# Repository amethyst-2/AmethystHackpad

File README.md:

<h1> Amethyst Hackpad  </h1>
Welcome to my project.  
Its a cutie made my be :)  
with amethyst colors as my name  

<h2> Design  </h2>
Below are all the images of hackpad  

Case :-  

Bottom layer :-  
  
For the pcb to rest on i have added a small ridge ( with chamfer on the below )  

Top layer :-  

<h2> Electronics </h2>  

Now let's get to the electronics part!  
Schematics ( Made in KiCad ) :-  

PCB :-  

<h2> Bill of Materials  </h2>
And finally here is the all the materials I used :-  

|      |Component Used            |      |Quantity|
|------|--------------------------|------|--------|
|      |                          |      |        |
|1     |Seeed XIAO RP2040         |      |1       |
|      |                          |      |        |
|2     |MX-Style switches         |      |16      |
|      |                          |      |        |
|3     |Through-hole 1N4148 Diodes|      |16      |
|      |                          |      |        |
|4     |0.91 inch OLED            |      |1       |
|      |                          |      |        |
|5     |Blank DSA keycaps         |      |16      |
|      |                          |      |        |
|6     |SK6812 MINI-E LEDs        |      |16      |

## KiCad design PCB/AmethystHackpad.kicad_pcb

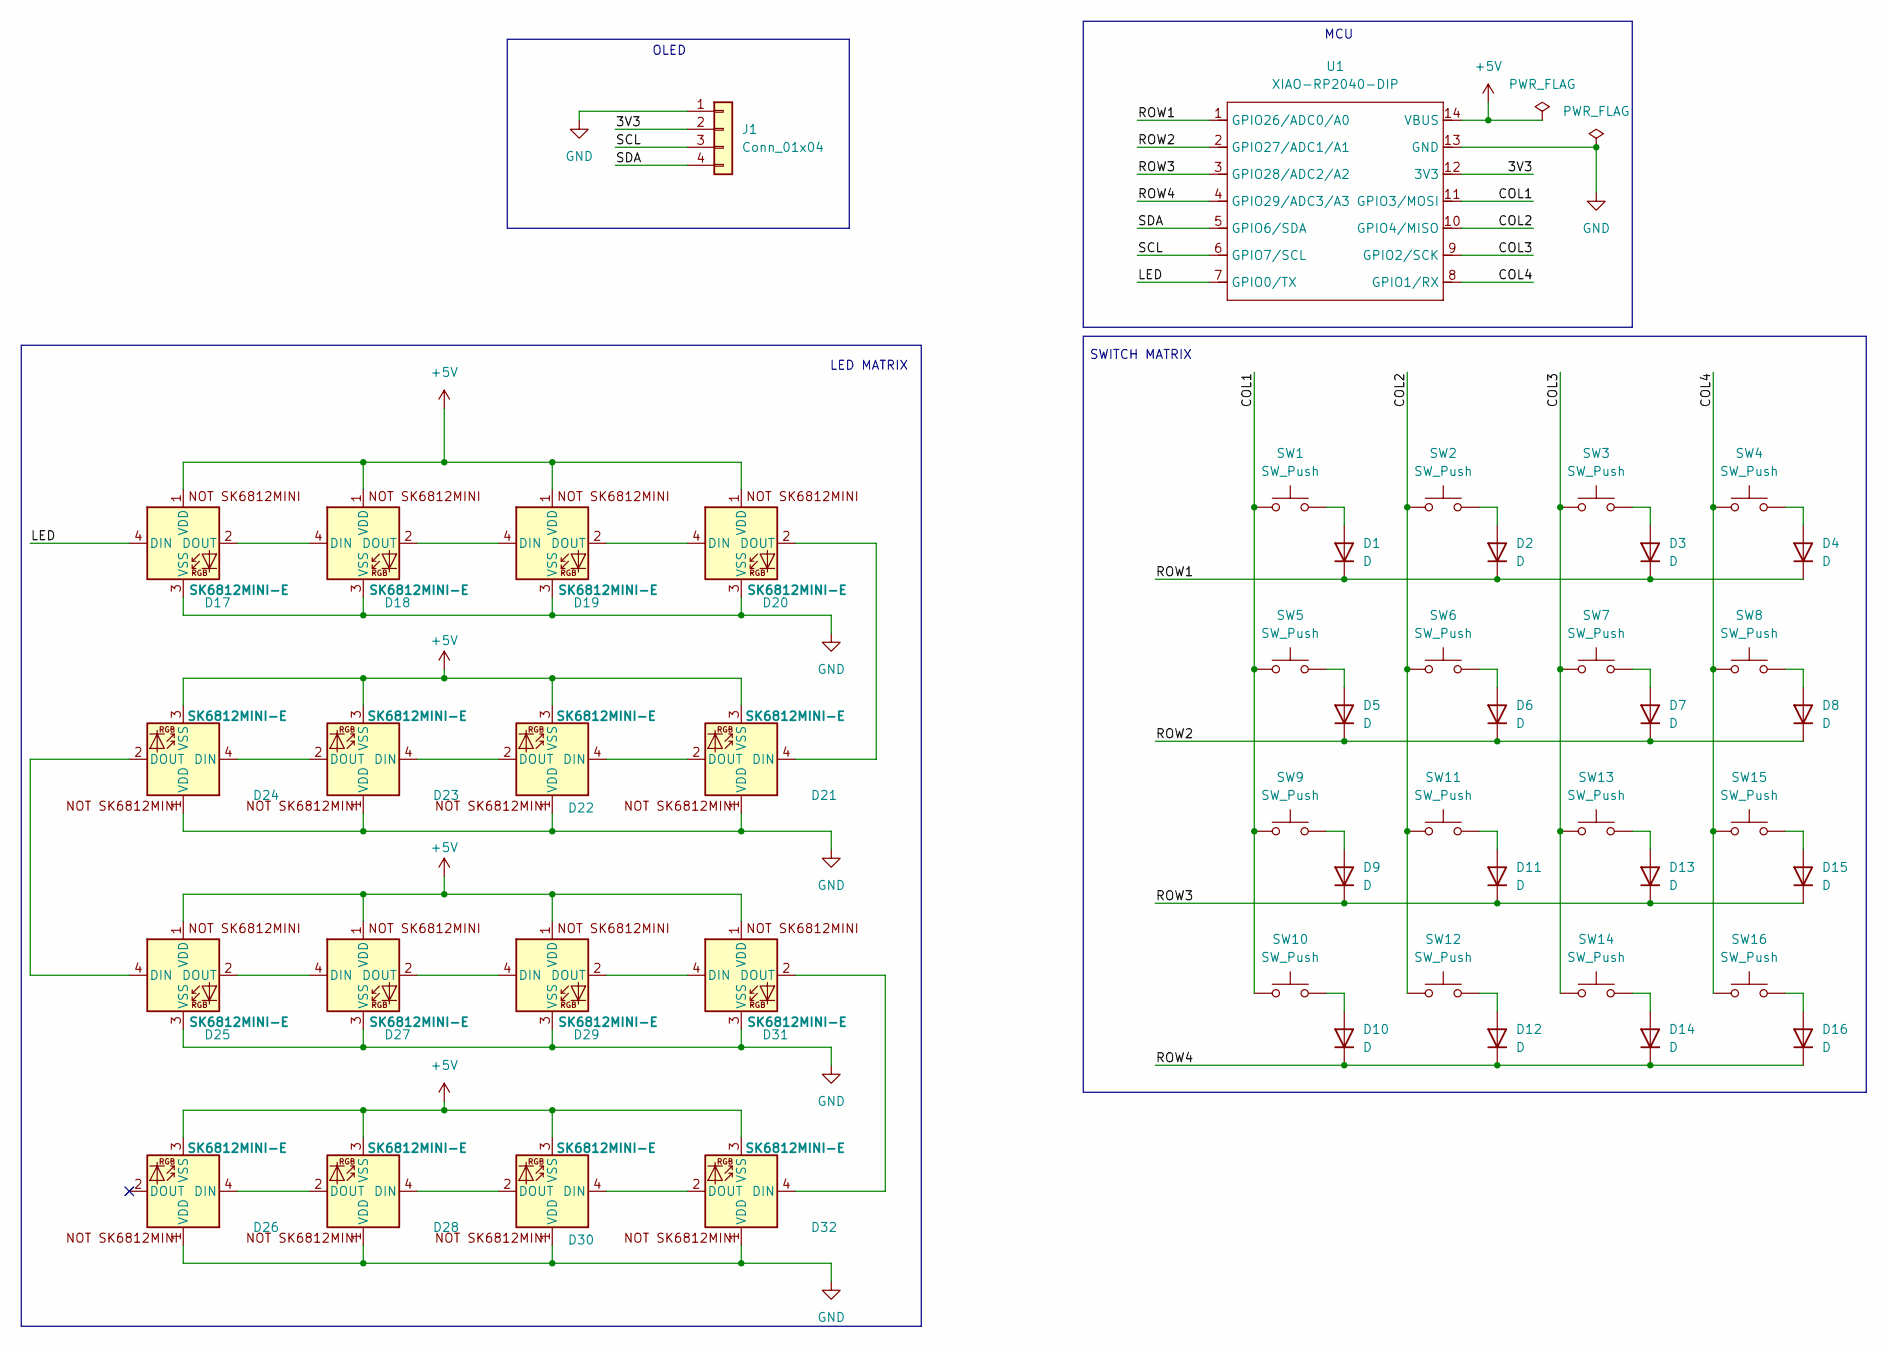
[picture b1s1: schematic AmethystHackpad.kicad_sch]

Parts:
D1, D2, D3, D4, D5, D6, D7, D8, D9, D10, D11, D12, D13, D14, D15, D16: D; D_DO-35_SOD27_P7.62mm_Horizontal
D17, D18, D19, D20, D21, D22, D23, D24, D25, D26, D27, D28, D29, D30, D31, D32: SK6812MINI-E; SK6812MINI-E_fixed
J1: Conn_01x04; PinHeader_1x04_P2.54mm_Vertical
SW1, SW2, SW3, SW4, SW5, SW6, SW7, SW8, SW9, SW10, SW11, SW12, SW13, SW14, SW15, SW16: SW_Push; SW_MX_1u
U1: XIAO-RP2040-DIP; XIAO-Generic-Hybrid-14P-2.54-21X17.8MM

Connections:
+5V: D17.1 (VDD), D18.1 (VDD), D19.1 (VDD), D20.1 (VDD), D21.3 (VSS), D22.3 (VSS), D23.3 (VSS), D24.3 (VSS), D25.1 (VDD), D26.3 (VSS), D27.1 (VDD), D28.3 (VSS), D29.1 (VDD), D30.3 (VSS), D31.1 (VDD), D32.3 (VSS), U1.14 (VBUS)
/3V3: J1.2, U1.12 (3V3)
/COL1: SW1.1, SW5.1, SW9.1, SW10.1, U1.11 (GPIO3/MOSI)
/COL2: SW2.1, SW6.1, SW11.1, SW12.1, U1.10 (GPIO4/MISO)
/COL3: SW3.1, SW7.1, SW13.1, SW14.1, U1.9 (GPIO2/SCK)
/COL4: SW4.1, SW8.1, SW15.1, SW16.1, U1.8 (GPIO1/RX)
/LED: D17.4 (DIN), U1.7 (GPIO0/TX)
/ROW1: D1.1 (K), D2.1 (K), D3.1 (K), D4.1 (K), U1.1 (GPIO26/ADC0/A0)
/ROW2: D5.1 (K), D6.1 (K), D7.1 (K), D8.1 (K), U1.2 (GPIO27/ADC1/A1)
/ROW3: D9.1 (K), D11.1 (K), D13.1 (K), D15.1 (K), U1.3 (GPIO28/ADC2/A2)
/ROW4: D10.1 (K), D12.1 (K), D14.1 (K), D16.1 (K), U1.4 (GPIO29/ADC3/A3)
/SCL: J1.3, U1.6 (GPIO7/SCL)
/SDA: J1.4, U1.5 (GPIO6/SDA)
GND: D17.3 (VSS), D18.3 (VSS), D19.3 (VSS), D20.3 (VSS), D21.1 (VDD), D22.1 (VDD), D23.1 (VDD), D24.1 (VDD), D25.3 (VSS), D26.1 (VDD), D27.3 (VSS), D28.1 (VDD), D29.3 (VSS), D30.1 (VDD), D31.3 (VSS), D32.1 (VDD), J1.1, U1.13 (GND)
unnamed: D1.2 (A), SW1.2
unnamed: D2.2 (A), SW2.2
unnamed: D3.2 (A), SW3.2
unnamed: D4.2 (A), SW4.2
unnamed: D5.2 (A), SW5.2
unnamed: D6.2 (A), SW6.2
unnamed: D7.2 (A), SW7.2
unnamed: D8.2 (A), SW8.2
unnamed: D9.2 (A), SW9.2
unnamed: D10.2 (A), SW10.2
unnamed: D11.2 (A), SW11.2
unnamed: D12.2 (A), SW12.2
unnamed: D13.2 (A), SW13.2
unnamed: D14.2 (A), SW14.2
unnamed: D15.2 (A), SW15.2
unnamed: D16.2 (A), SW16.2
unnamed: D17.2 (DOUT), D18.4 (DIN)
unnamed: D18.2 (DOUT), D19.4 (DIN)
unnamed: D19.2 (DOUT), D20.4 (DIN)
unnamed: D20.2 (DOUT), D21.4 (DIN)
unnamed: D21.2 (DOUT), D22.4 (DIN)
unnamed: D22.2 (DOUT), D23.4 (DIN)
unnamed: D23.2 (DOUT), D24.4 (DIN)
unnamed: D24.2 (DOUT), D25.4 (DIN)
unnamed: D25.2 (DOUT), D27.4 (DIN)
unnamed: D26.4 (DIN), D28.2 (DOUT)
unnamed: D27.2 (DOUT), D29.4 (DIN)
unnamed: D28.4 (DIN), D30.2 (DOUT)
unnamed: D29.2 (DOUT), D31.4 (DIN)
unnamed: D30.4 (DIN), D32.2 (DOUT)
unnamed: D31.2 (DOUT), D32.4 (DIN)

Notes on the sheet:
SWITCH MATRIX
MCU
OLED
LED MATRIX

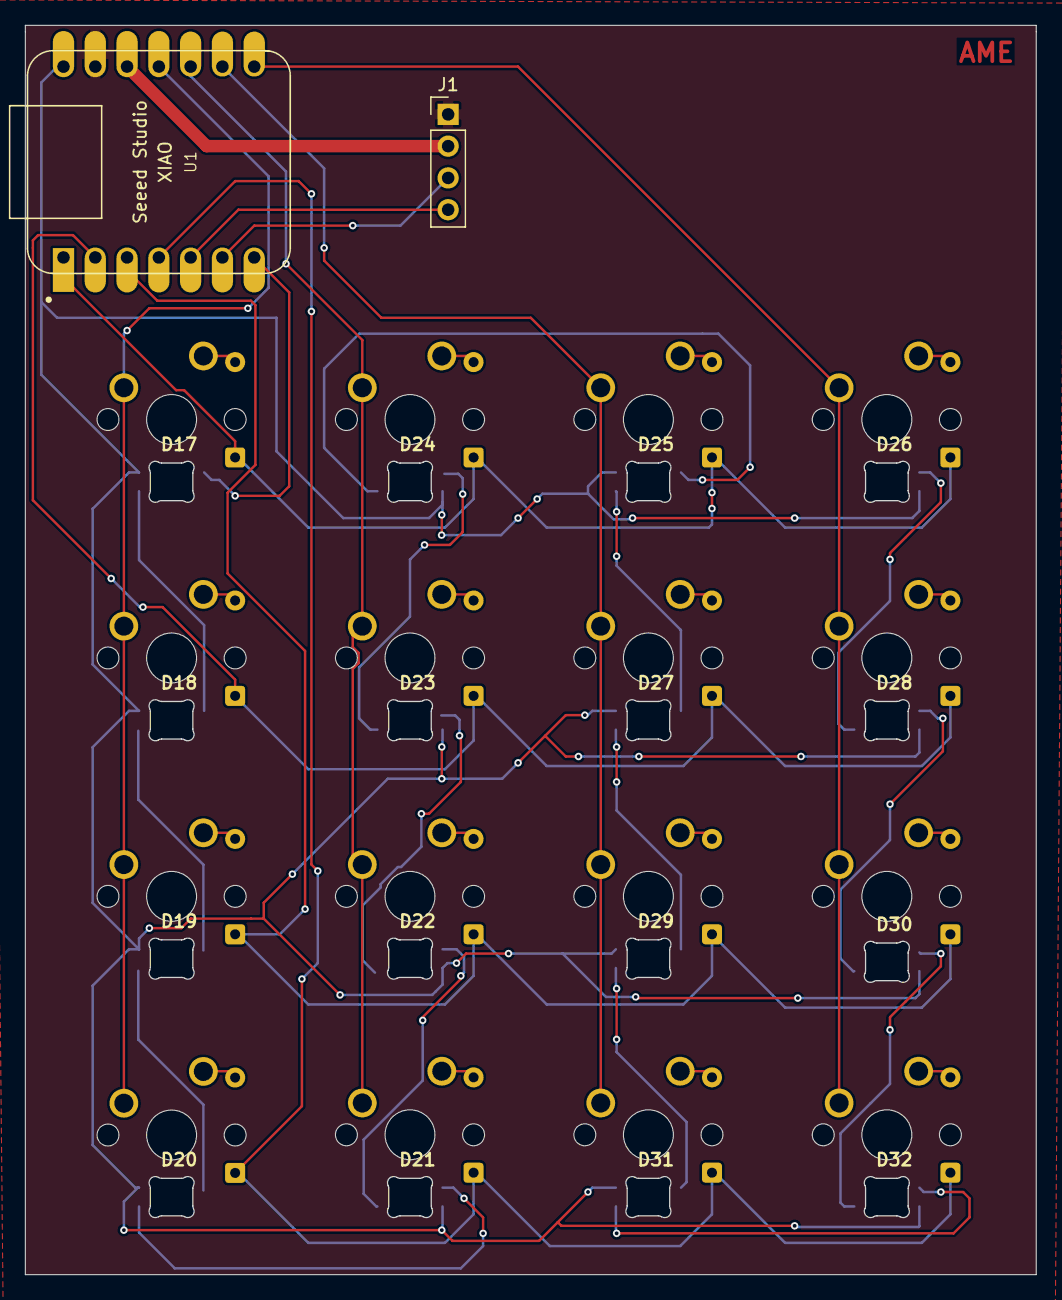
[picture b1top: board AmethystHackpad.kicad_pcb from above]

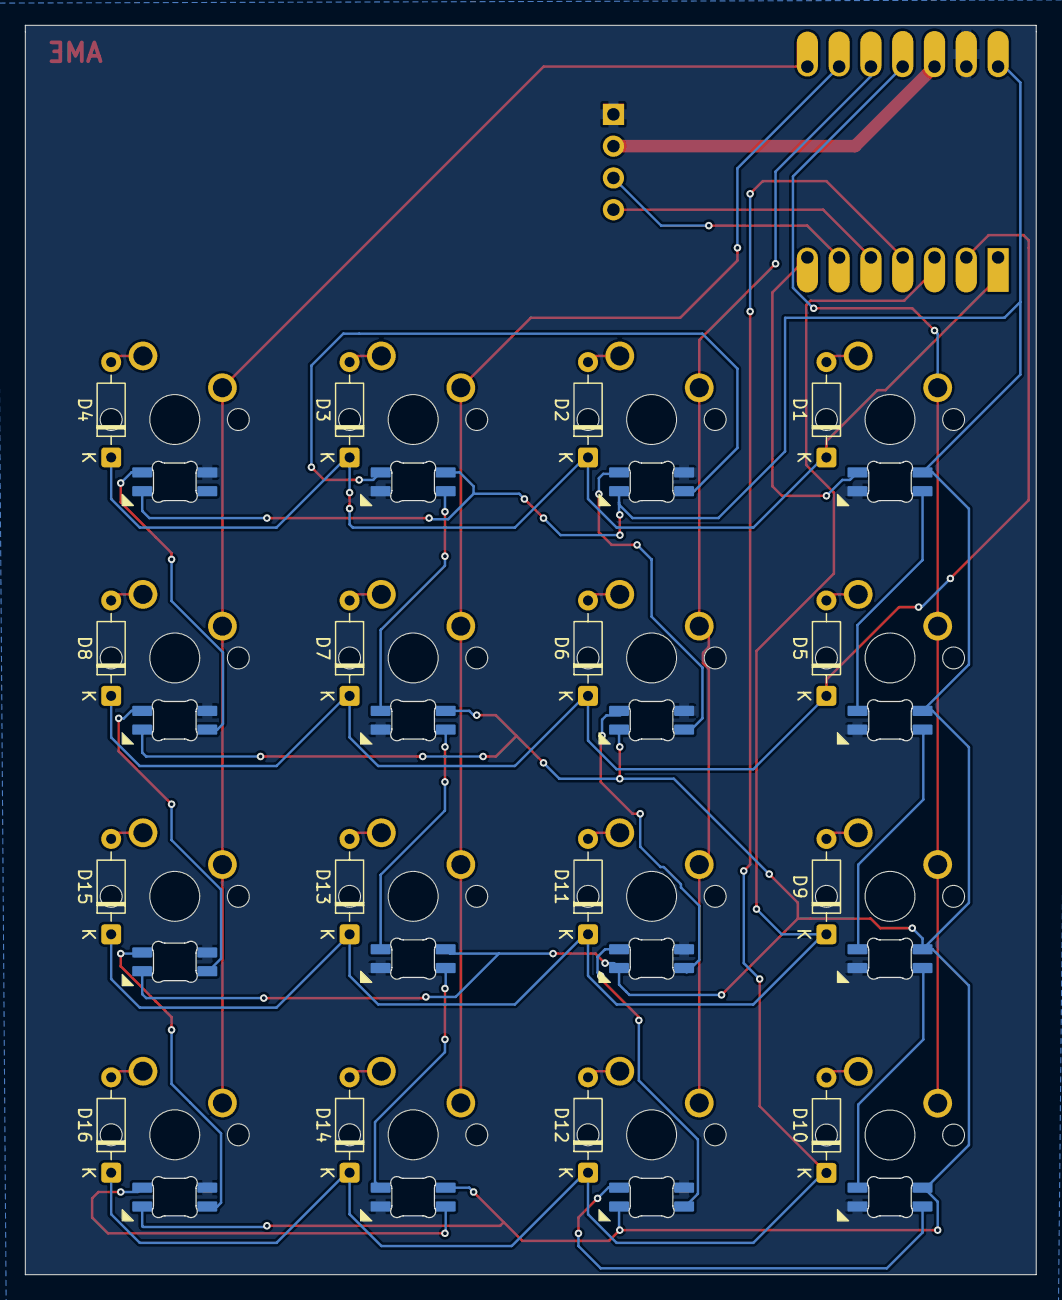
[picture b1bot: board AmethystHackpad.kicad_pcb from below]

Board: 2 copper layers, 80.7 x 99.8 mm, 50 parts (16 on the bottom side), 45 nets.

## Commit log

2025-12-29 Uploaded files from local repo
